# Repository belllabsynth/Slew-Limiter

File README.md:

# Slew Limiter

This is a simple eurorack slew limiter, with a very low parts count that is quick and easy to build. There are no extra frills, just a pot for slew amount, a toggle switch to select between slewing up, down, or both, one input, and one output. 

I drew the schematic from a stripboard layout done by user Mcshafty on the Look Mum No Computer discourse forums ([link here](https://lookmumnocomputer.discourse.group/t/slew-generator-stripboard-confirmed-working/1865)), which is based off of schematics from [Dintree](https://dintree.com) and [YuSynth](https://yusynth.com).

*General Notes:* 

* Current revision (v1.2) of board is untested as of yet, though past versions have worked as expected. I will update and remove this text when I get my new boards in.
* The included Gerber files have been generated for JLCPCB and have not been tested with manufacturers. I have included silkscreen text on the back of both the main board and the panel to avoid JLC printing the batch number on the front. Remove the text saying "JLCJLCJLCJLC" if printing elsewhere and you care to have that removed.
* JLCPCB does not detect the pcb size for the front panel. You can enter it as 128x20mm.
* Depending on your rack, the v1.0 and v1.1 boards may have been too long and not clear your rails. There are no traces below the output jacks ground leg and you can carefully cut a little bit off the board below there if needed. This have been fixed in v1.2.

*Changes In v1.2:*

* Change C4 and C5 from polarized 10uf capacitors to one (now C3) bipolar 4.7uf capacitor
* Resize main board PCB to 100mm height to fix potential clearance issue and reduce manufacturing cost
* Re-design board to make the build a little bit easier
* Change power header footprint to a shrouded header, taken from the [Winterbloom GitHub](https://github.com/wntrblm)
* Increase silkscreen text size and edgecut line thickness to avoid possible issues at certain PCB houses
* Add "JLCJLCJLCJLC" text to main board PCB and front panel so JLC doesn't put their batch number on the front
* Misc schematic changes to improve readability

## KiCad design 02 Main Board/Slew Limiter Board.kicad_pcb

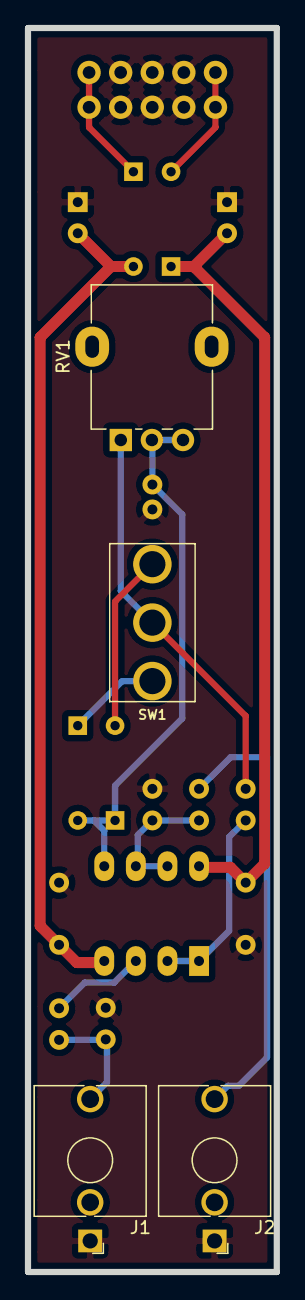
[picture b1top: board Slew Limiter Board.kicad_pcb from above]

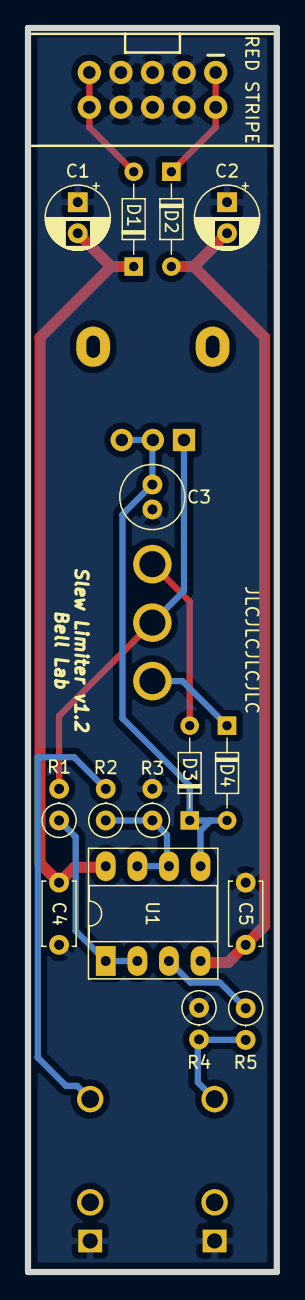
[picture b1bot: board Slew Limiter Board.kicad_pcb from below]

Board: 2 copper layers, 20.0 x 100.0 mm, 20 parts (16 on the bottom side), 14 nets.

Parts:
C1, C2: 10uf; CP_Radial_D5.0mm_P2.50mm
C3: 4.7uf; C_Radial_D5.0mm_H11.0mm_P2.00mm
C4, C5: 100nf; C_Disc_D5.0mm_W2.5mm_P5.00mm
D1, D2: 1N5817; D_DO-34_SOD68_P7.62mm_Horizontal
D3, D4: 1N4148; D_DO-34_SOD68_P7.62mm_Horizontal
J1: Input; Jack_3.5mm_QingPu_WQP-PJ398SM_Vertical_CircularHoles
J2: Output; Jack_3.5mm_QingPu_WQP-PJ398SM_Vertical_CircularHoles
JP1: PWR; Eurorack_Power
R1, R2: 100r; R_Axial_DIN0207_L6.3mm_D2.5mm_P2.54mm_Vertical
R3, R4: 100k; R_Axial_DIN0207_L6.3mm_D2.5mm_P2.54mm_Vertical
R5: 1k; R_Axial_DIN0207_L6.3mm_D2.5mm_P2.54mm_Vertical
RV1: 250k lin; Potentiometer_Alpha_RD901F-40-00D_Single_Vertical
SW1: ON-OFF-ON; SPDT-toggle-switch-1M-series
U1: TL072; DIP-8_W7.62mm_Socket_LongPads

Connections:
+12V: C1.2, C4.1, D1.1, U1.8
-12V: C2.2, C5.1, D2.2, U1.4
GND: C1.1, C2.1, C3.2, C4.2, C5.2, J1.S, J2.S, JP1.3, JP1.4, JP1.5, JP1.6, JP1.7, JP1.8, R3.2, R4.1
unnamed: C3.1, D3.1, D4.2, RV1.2, RV1.3, U1.5
unnamed: D1.2, JP1.9, JP1.10
unnamed: D2.1, JP1.1, JP1.2
unnamed: D3.2, SW1.1
unnamed: D4.1, SW1.3
unnamed: J1.T, R4.2, R5.2
unnamed: J2.T, R2.2
unnamed: R1.1, U1.1, U1.2
unnamed: R1.2, RV1.1, SW1.2
unnamed: R2.1, R3.1, U1.6, U1.7
unnamed: R5.1, U1.3

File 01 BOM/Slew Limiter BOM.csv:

Reference(s),Value,Qty,Description
"C1, C2",10uf,2,Polarized radial capacitor
C3,4.7uf,1,Bipolar radial capacitor
"C4, C5",100nf,2,Ceramic disc capacitor
"D1, D2",1N5817,2,Diode
"D3, D4",1N4148,2,Diode
J1,Input,1,Thonkiconn
J2,Output,1,Thonkiconn
JP1,PWR,1,Power header
"R1, R2",100r,2,1/4w resistor
"R3, R4",100k,2,1/4w resistor
R5,1k,1,1/4w resistor
RV1,250k lin,1,Alpha 9mm vertical pot
SW1,ON-OFF-ON,1,SPDT switch – Tayda 1M series
U1,TL072,1,OpAmp

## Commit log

2021-10-10 misc changes see description
    Slightly shrink board (no moving of components)
    Increase silkscreen text size
    Increase edge cuts line thickness
2021-10-16 Update README.md
    formatting
2021-10-20 Update to v1.2
    Many changes, see readme for list
2021-10-20 Front panel text fix
    Nudge input and output text
